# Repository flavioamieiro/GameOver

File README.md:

Hardware for Game Over project

[BaseBoard](BaseBoard/) contains the design files for the  main board, which
has an ESP32 and will be the base for the add-ons.

[BNO055Sensor](BNO055Sensor/) is the first add-on: basically a BNO055 sensor
from Adafruit used for motion detection.

[Keypad](Keypad/) is a keypad with six buttons and LEDs to be used as
an interface.

[BreakoutBoard](BreakoutBoard/) is a simple breakout board for easier
prototyping using the base board.

[AddonTemplate](AddonTemplate/) is a kicad template you can use as a base to
create new addon boards.

This source describes Open Hardware and is licensed under the CERN-OHL-S v2.
You may redistribute and modify this source and make products using it under
the terms of the [CERN-OHL-S v2](https://ohwr.org/cern_ohl_s_v2.txt).

Source location: https://github.com/flavioamieiro/GameOver

As per CERN-OHL-S v2 section 4, should You produce hardware based on this
source, You must where practicable maintain the Source Location visible on the
external case of the Gizmo or other products you make using this source.

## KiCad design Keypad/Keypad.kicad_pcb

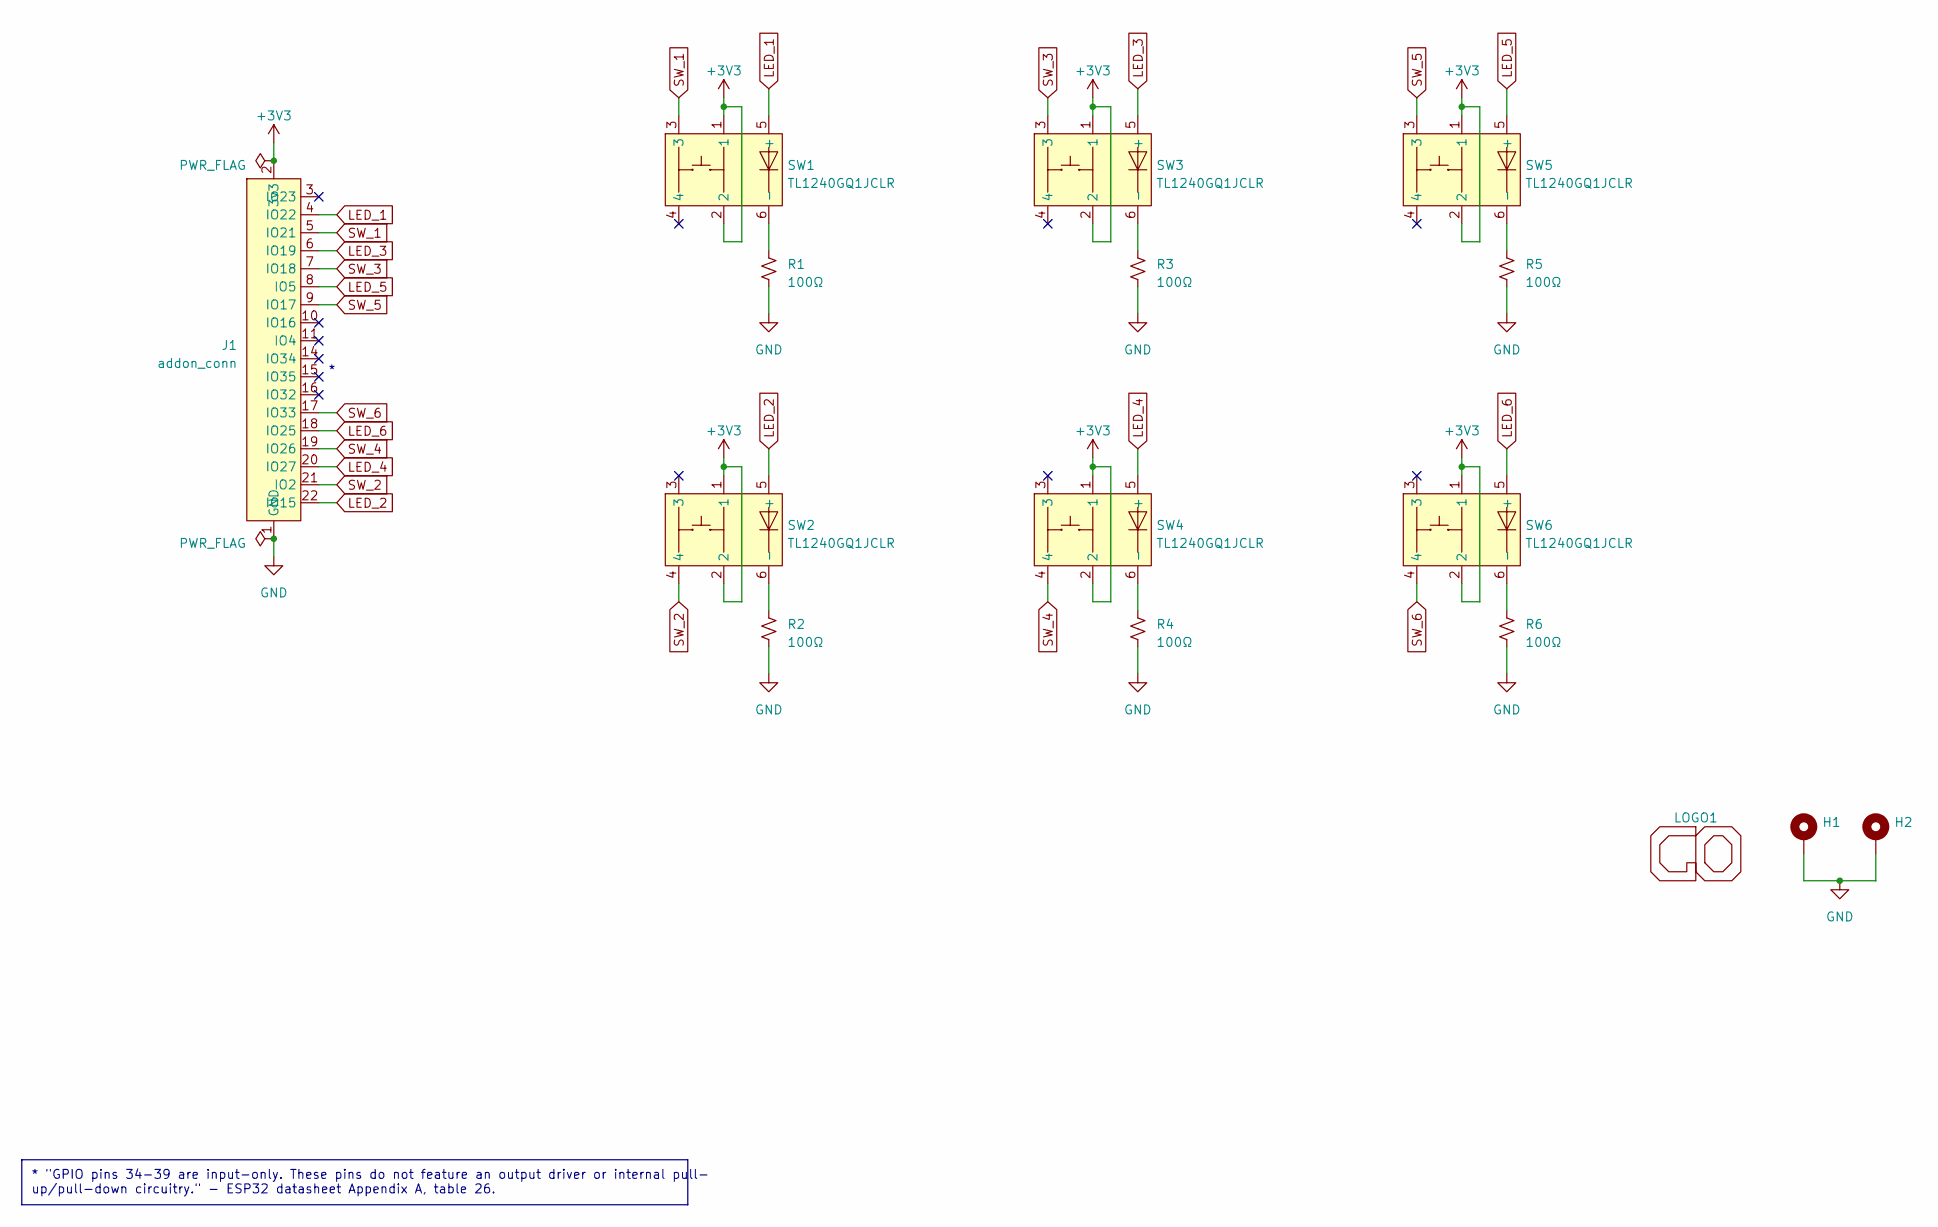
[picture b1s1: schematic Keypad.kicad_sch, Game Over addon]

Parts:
H1, H2: MountingHole_2.2mm_M2_Pad_Via
J1: addon_conn; Addon_conn_TXGA_FFC05036-24SBD113W5M_1x24_P0.50mm_Horizontal
LOGO1: GameOver_logo; logo_fcu
R1, R2, R3, R4, R5, R6: 100Ω; R_0805_2012Metric_Pad1.20x1.40mm_HandSolder
SW1, SW2, SW3, SW4, SW5, SW6: TL1240GQ1JCLR

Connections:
+3V3: J1.2 (3v3), J1.13 (3v3), J1.24 (3v3), SW1.1, SW1.2, SW2.1, SW2.2, SW3.1, SW3.2, SW4.1, SW4.2, SW5.1, SW5.2, SW6.1, SW6.2
GND: H1.1, H2.1, J1.1 (GND), J1.12 (GND), J1.23 (GND), R1.2, R2.2, R3.2, R4.2, R5.2, R6.2
LED_1: J1.4 (IO22), SW1.5 (+)
LED_2: J1.22 (IO15), SW2.5 (+)
LED_3: J1.6 (IO19), SW3.5 (+)
LED_4: J1.20 (IO27), SW4.5 (+)
LED_5: J1.8 (IO18), SW5.5 (+)
LED_6: J1.18 (IO25), SW6.5 (+)
unnamed: R1.1, SW1.6 (-)
unnamed: R2.1, SW2.6 (-)
unnamed: R3.1, SW3.6 (-)
unnamed: R4.1, SW4.6 (-)
unnamed: R5.1, SW5.6 (-)
unnamed: R6.1, SW6.6 (-)
SW_1: J1.5 (IO21), SW1.3
SW_2: J1.21 (IO2), SW2.4
SW_3: J1.7 (IO5), SW3.3
SW_4: J1.19 (IO26), SW4.4
SW_5: J1.9 (IO17), SW5.3
SW_6: J1.17 (IO33), SW6.4

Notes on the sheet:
* "GPIO pins 34-39 are input-only. These pins do not feature an output driver or internal pull- up/pull-down circuitry." - ESP32 datasheet Appendix A, table 26.

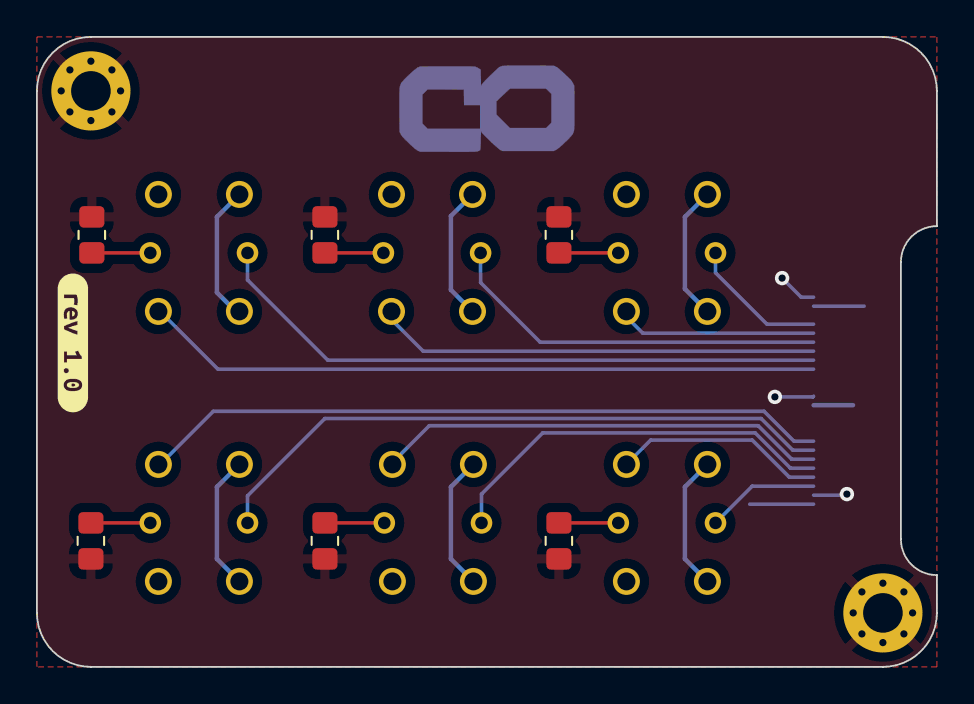
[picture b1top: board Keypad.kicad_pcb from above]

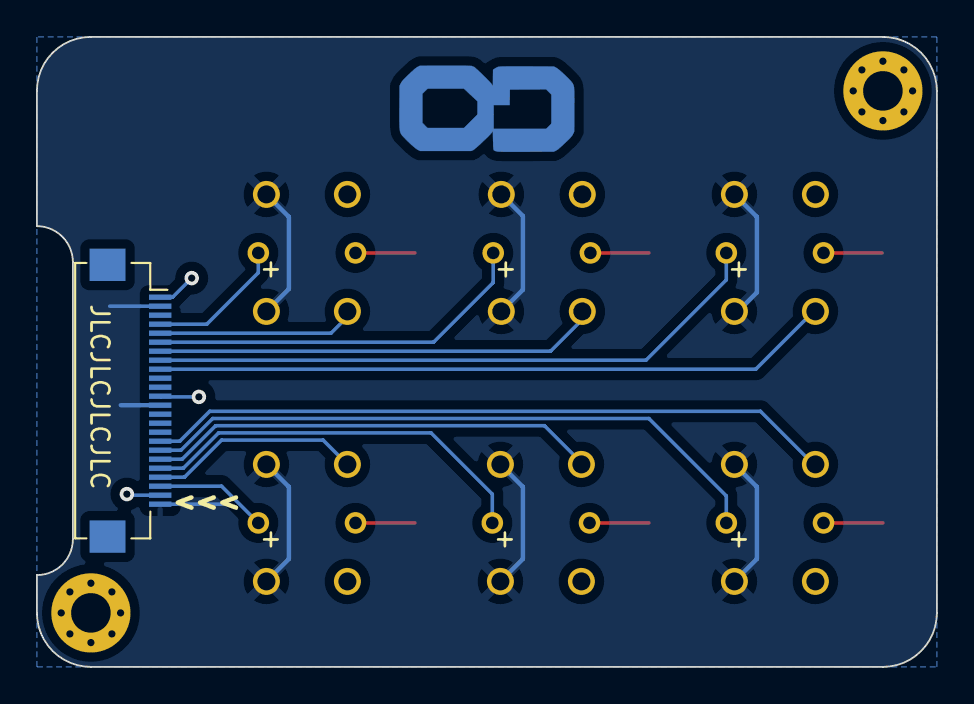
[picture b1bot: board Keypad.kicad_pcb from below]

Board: 2 copper layers, 50.0 x 35.0 mm, 17 parts (8 on the bottom side), 20 nets.

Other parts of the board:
kibuzzard-63029D1F: G***; kibuzzard-63029D1F

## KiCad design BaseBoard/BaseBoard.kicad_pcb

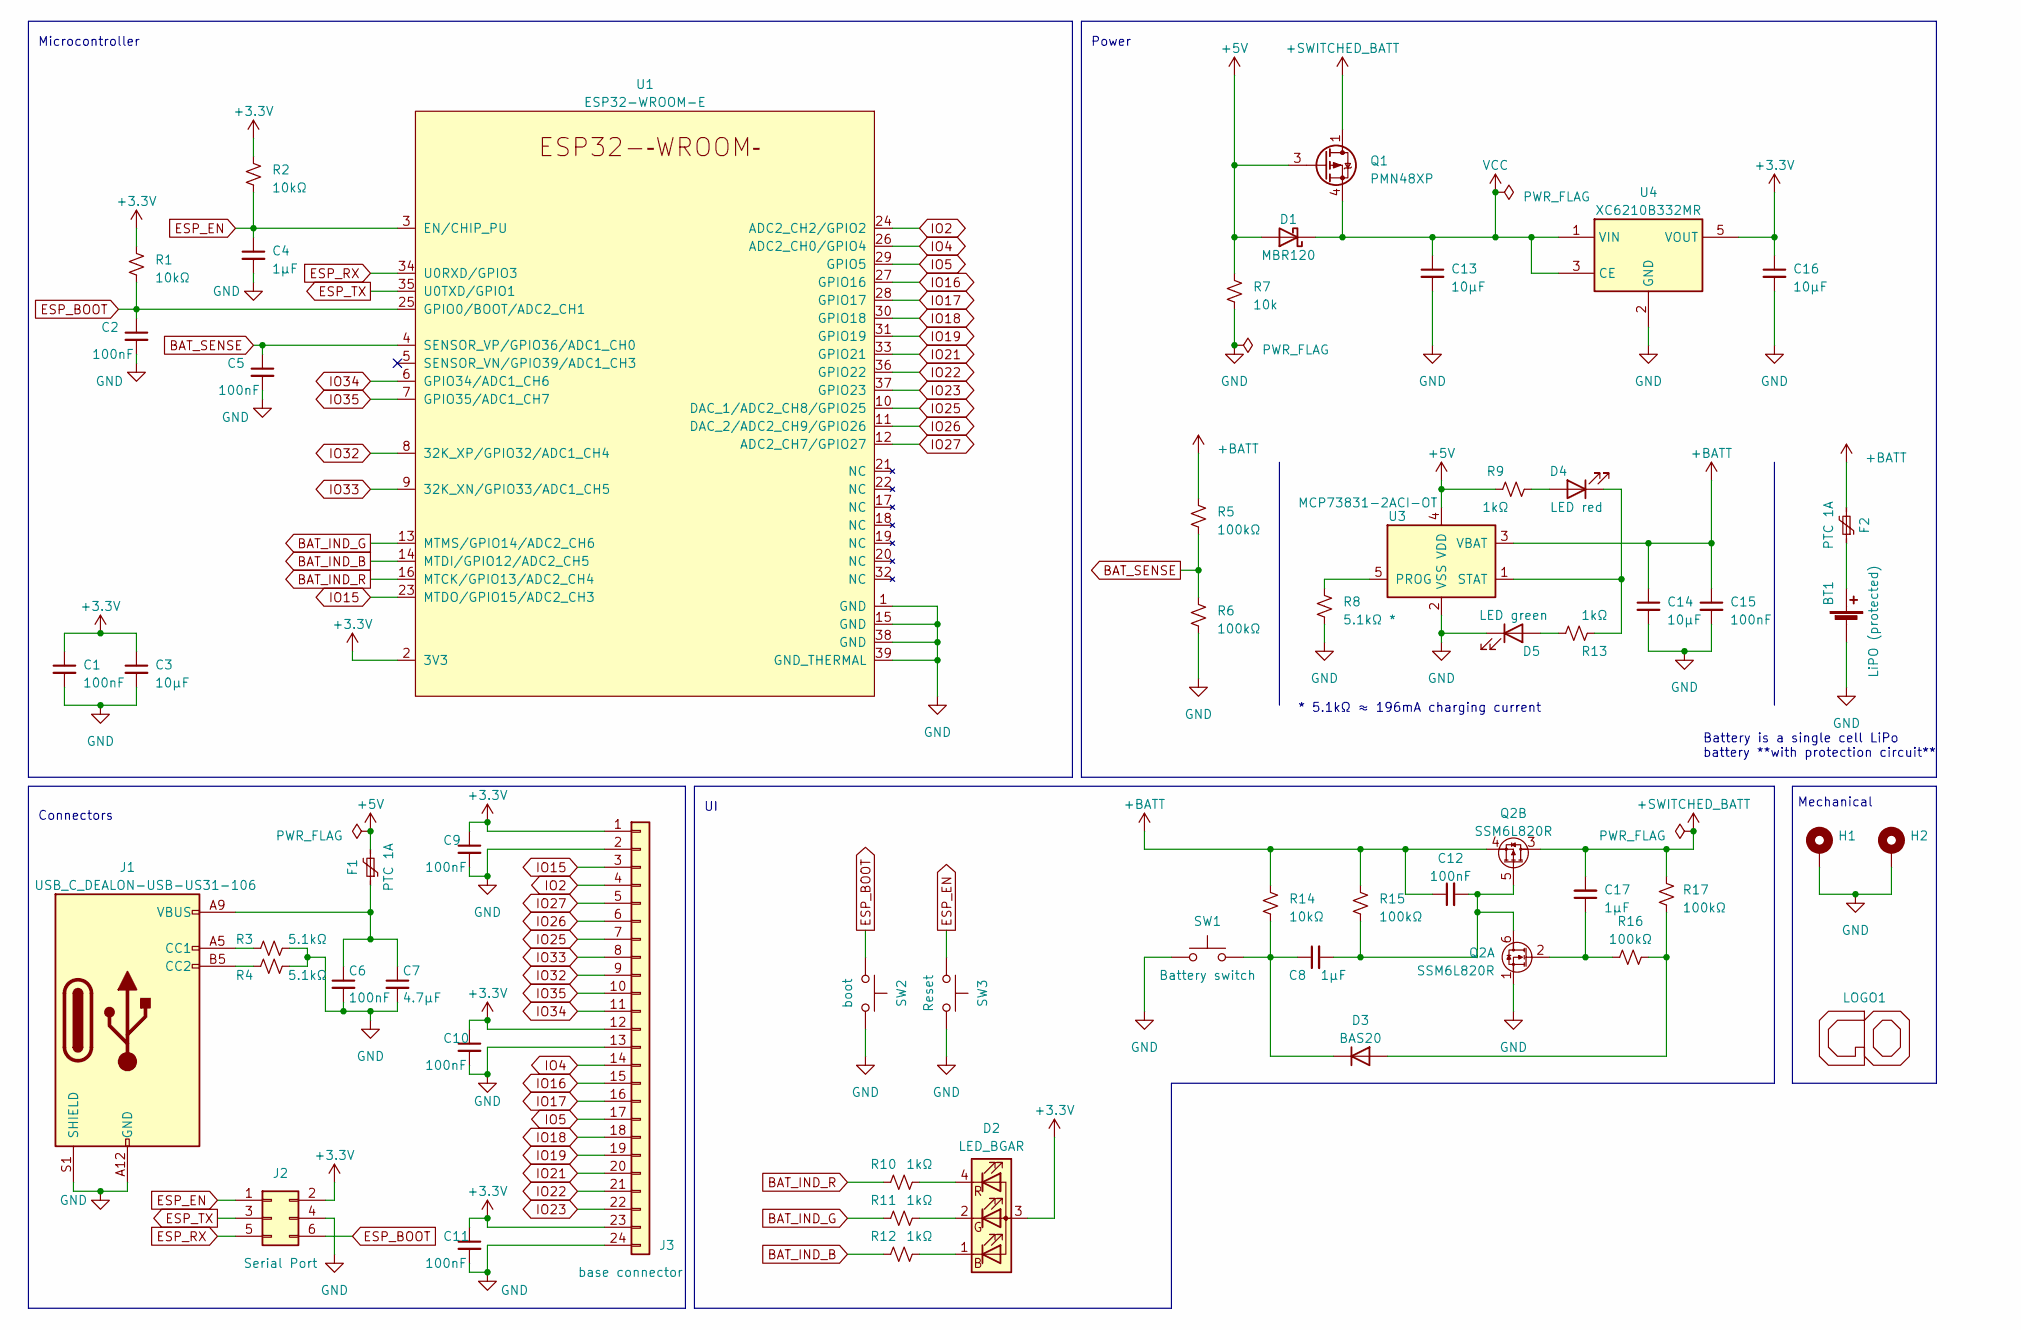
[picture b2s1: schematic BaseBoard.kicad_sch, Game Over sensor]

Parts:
BT1: LiPO (protected); JST_PH_S2B-PH-SM4-TB_1x02-1MP_P2.00mm_Horizontal
C1, C2, C5, C6, C9, C10, C11, C12, C15: 100nF; C_0805_2012Metric_Pad1.18x1.45mm_HandSolder
C3, C13, C14, C16: 10µF; C_0805_2012Metric_Pad1.18x1.45mm_HandSolder
C4, C8, C17: 1µF; C_0805_2012Metric_Pad1.18x1.45mm_HandSolder
C7: 4.7µF; C_0805_2012Metric_Pad1.18x1.45mm_HandSolder
D1: MBR120; D_SOD-123
D2: LED_BGAR; Hongzhi_Forest_HS-1204-RGB
D3: BAS20; SOT-23
D4: LED red; LED_0603_1608Metric
D5: LED green; LED_0603_1608Metric
F1, F2: PTC 1A; Belfuse_0ZCJ
H1, H2: MountingHole_2.2mm_M2_Pad_Via
J1: USB_C_DEALON-USB-US31-106; DEALON_USB-US31-106
J2: Serial Port; Tag-Connect_TC2030-IDC-FP_2x03_P1.27mm_Vertical
J3: base connector; Base_conn_TXGA_FFC05036-24SBD113W5M_1x24_P0.50mm_Horizontal
LOGO1: GameOver_logo; logo_fsilk
Q1: PMN48XP; TSOP-6_1.65x3.05mm_P0.95mm
Q2: SSM6L820R; TSOP6F
R1, R2, R14: 10kΩ; R_0805_2012Metric_Pad1.20x1.40mm_HandSolder
R3, R4: 5.1kΩ; R_0805_2012Metric_Pad1.20x1.40mm_HandSolder
R5, R6, R15, R16, R17: 100kΩ; R_0805_2012Metric_Pad1.20x1.40mm_HandSolder
R7: 10k; R_0805_2012Metric_Pad1.20x1.40mm_HandSolder
R8: 5.1kΩ *; R_0805_2012Metric_Pad1.20x1.40mm_HandSolder
R9, R10, R11, R12, R13: 1kΩ; R_0805_2012Metric_Pad1.20x1.40mm_HandSolder
SW1: Battery switch; SW_Tactile_SPST_SOFNG_TS-1814
SW2: boot; SW_Tactile_SPST_SOFNG_TS-1814
SW3: Reset; SW_Tactile_SPST_SOFNG_TS-1814
U1: ESP32-WROOM-E; ESP32-WROOM-32E
U3: MCP73831-2ACI-OT; SOT-23-5
U4: XC6210B332MR; SOT-23-5

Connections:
+3V3: C1.1, C3.1, C9.1, C10.1, C11.1, C16.1, D2.3 (A), J2.2, J3.1, J3.12, J3.23, R1.1, R2.1, U1.2 (3V3), U4.5 (VOUT)
+5V: D1.2 (A), F1.2, Q1.3 (G), R7.1, R9.2, U3.4 (VDD)
+BATT: C12.1, C14.1, C15.1, F2.2, Q2.4 (S), R5.1, R14.1, R15.1, U3.3 (VBAT)
+SWITCHED_BATT: C17.2, Q1.1 (D), Q1.2 (D), Q1.5 (D), Q1.6 (D), Q2.3 (D), R17.2
BAT_IND_B: R12.1, U1.14 (MTDI/GPIO12/ADC2_CH5)
BAT_IND_G: R11.1, U1.13 (MTMS/GPIO14/ADC2_CH6)
BAT_IND_R: R10.1, U1.16 (MTCK/GPIO13/ADC2_CH4)
BAT_SENSE: C5.1, R5.2, R6.1, U1.4 (SENSOR_VP/GPIO36/ADC1_CH0)
ESP_BOOT: C2.1, J2.6, R1.2, SW2.1, U1.25 (GPIO0/BOOT/ADC2_CH1)
ESP_EN: C4.1, J2.1, R2.2, SW3.1, U1.3 (EN/CHIP_PU)
ESP_RX: J2.5, U1.34 (U0RXD/GPIO3)
ESP_TX: J2.3, U1.35 (U0TXD/GPIO1)
GND: BT1.2 (-), C1.2, C2.2, C3.2, C4.2, C5.2, C6.2, C7.2, C9.2, C10.2, C11.2, C13.2, C14.2, C15.2, C16.2, D5.1 (K), H1.1, H2.1, J1.A12 (GND), J1.B12 (GND), J1.S1 (SHIELD), J2.4, J3.2, J3.13, J3.24, Q2.1 (S), R3.2, R4.2, R6.2, R7.2, R8.2, SW1.1, SW2.2, SW3.2, U1.1 (GND), U1.15 (GND), U1.38 (GND), U1.39 (GND_THERMAL), U3.2 (VSS), U4.2 (GND)
IO2: J3.4, U1.24 (ADC2_CH2/GPIO2)
IO4: J3.14, U1.26 (ADC2_CH0/GPIO4)
IO5: J3.17, U1.29 (GPIO5)
IO15: J3.3, U1.23 (MTDO/GPIO15/ADC2_CH3)
IO16: J3.15, U1.27 (GPIO16)
IO17: J3.16, U1.28 (GPIO17)
IO18: J3.18, U1.30 (GPIO18)
IO19: J3.19, U1.31 (GPIO19)
IO21: J3.20, U1.33 (GPIO21)
IO22: J3.21, U1.36 (GPIO22)
IO23: J3.22, U1.37 (GPIO23)
IO25: J3.7, U1.10 (DAC_1/ADC2_CH8/GPIO25)
IO26: J3.6, U1.11 (DAC_2/ADC2_CH9/GPIO26)
IO27: J3.5, U1.12 (ADC2_CH7/GPIO27)
IO32: J3.9, U1.8 (32K_XP/GPIO32/ADC1_CH4)
IO33: J3.8, U1.9 (32K_XN/GPIO33/ADC1_CH5)
IO34: J3.11, U1.6 (GPIO34/ADC1_CH6)
IO35: J3.10, U1.7 (GPIO35/ADC1_CH7)
unnamed: BT1.1 (+), F2.1
unnamed: D2.1 (BK), R12.2
unnamed: D2.2 (GK), R11.2
unnamed: D2.4 (RK), R10.2
unnamed: D3.1 (A), R16.2, R17.1
unnamed: C8.1, D3.3 (K), R14.2, SW1.2
unnamed: D4.2 (A), R9.1
unnamed: D4.1 (K), R13.2, U3.1 (STAT)
unnamed: D5.2 (A), R13.1
unnamed: J1.A5 (CC1), R3.1
unnamed: J1.B5 (CC2), R4.1
unnamed: C6.1, C7.1, F1.1, J1.A9 (VBUS), J1.B9 (VBUS)
unnamed: C8.2, C12.2, Q2.5 (G), Q2.6 (D), R15.2
unnamed: C17.1, Q2.2 (G), R16.1
unnamed: R8.1, U3.5 (PROG)
VCC: C13.1, D1.1 (K), Q1.4 (S), U4.1 (VIN), U4.3 (CE)

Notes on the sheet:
Microcontroller
Connectors
Battery is a single cell LiPo battery **with protection circuit**
Power
* 5.1kΩ ≈ 196mA charging current
Mechanical

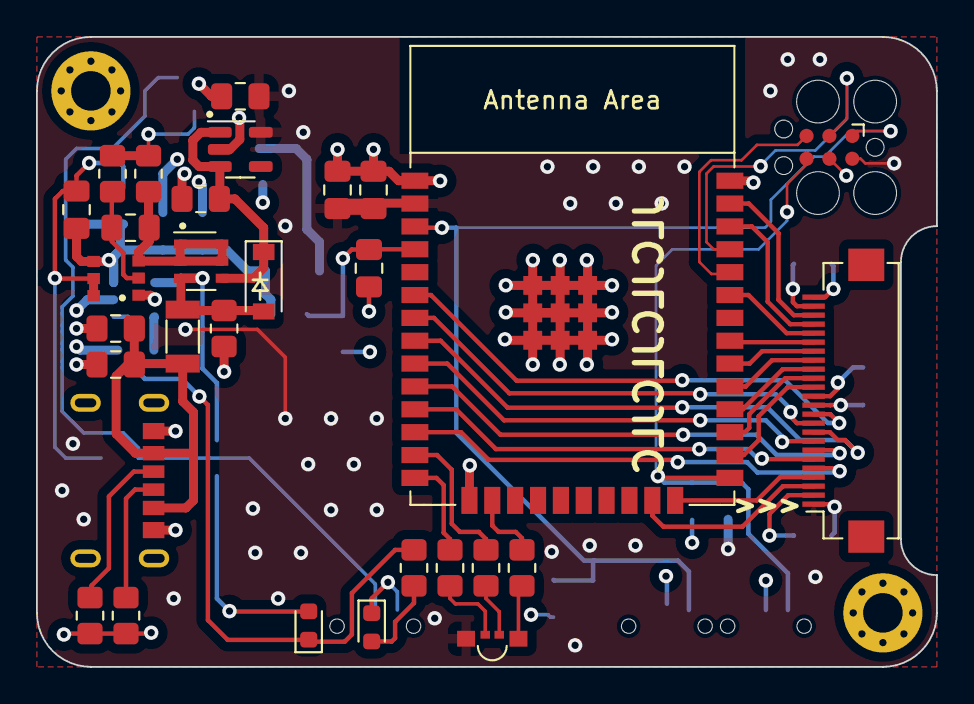
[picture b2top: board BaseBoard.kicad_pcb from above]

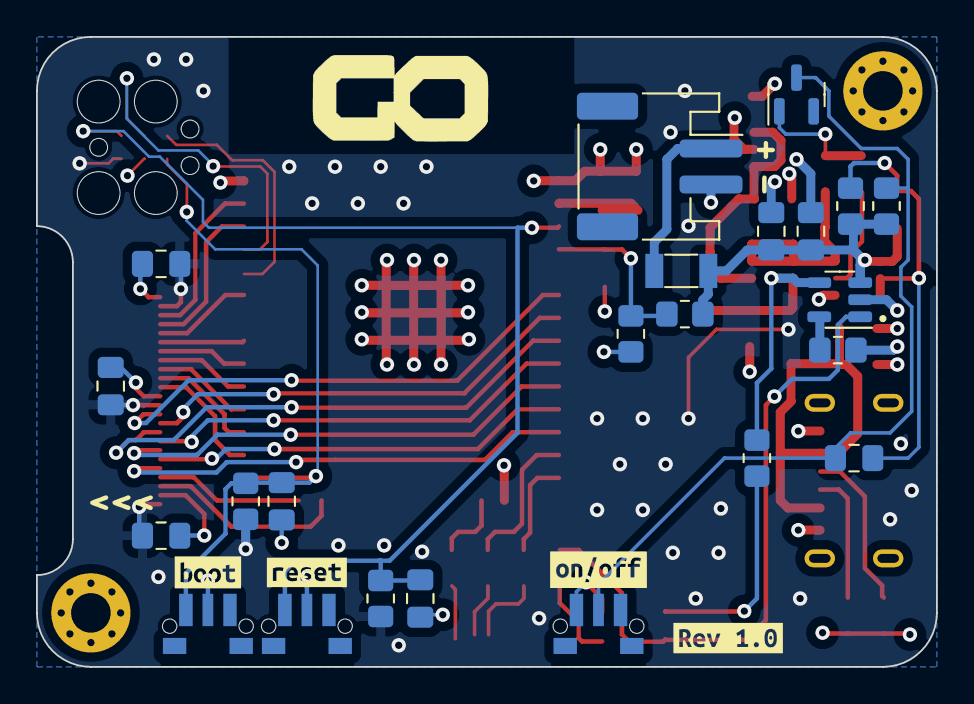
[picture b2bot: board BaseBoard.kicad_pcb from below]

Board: 4 copper layers, 50.0 x 35.0 mm, 60 parts (28 on the bottom side), 47 nets.

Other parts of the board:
kibuzzard-6253FE4C: G***; kibuzzard-6253FE4C
kibuzzard-6253FE42: G***; kibuzzard-6253FE42
kibuzzard-63029C06: G***; kibuzzard-63029C06
kibuzzard-63029CBF: G***; kibuzzard-63029CBF

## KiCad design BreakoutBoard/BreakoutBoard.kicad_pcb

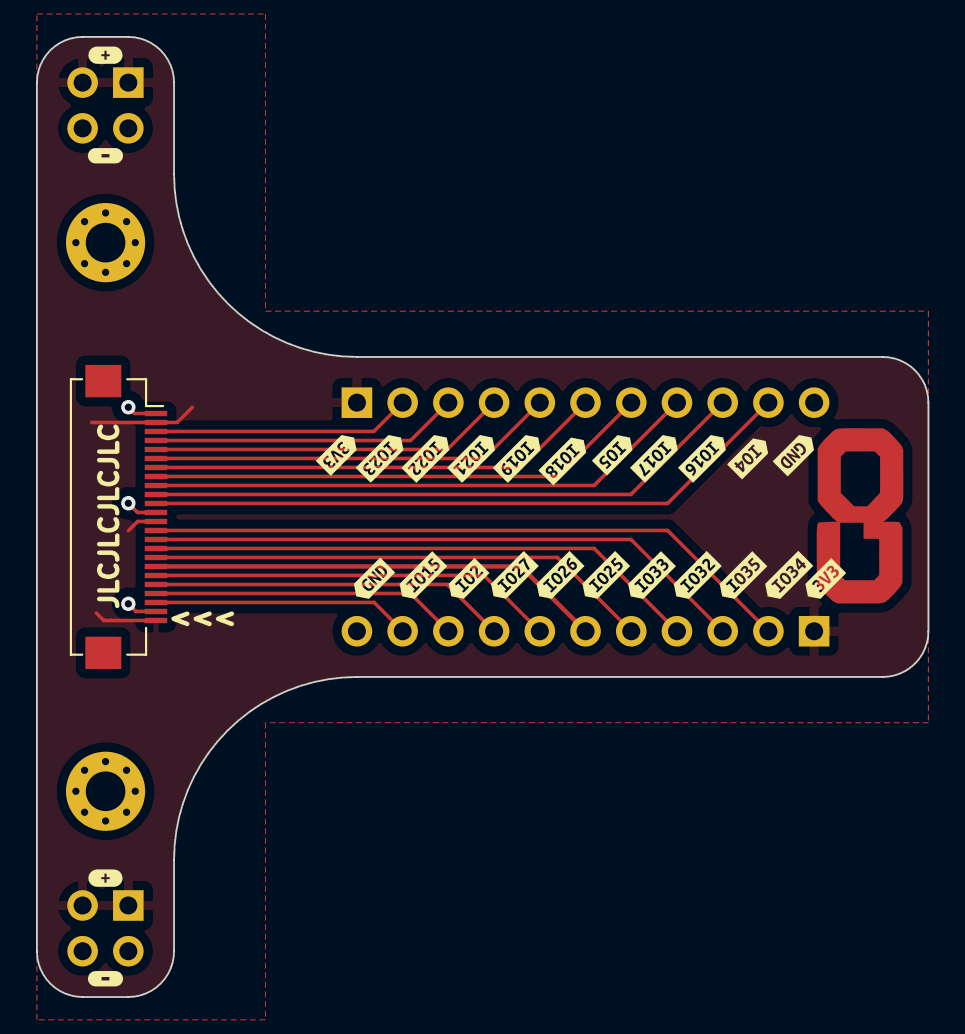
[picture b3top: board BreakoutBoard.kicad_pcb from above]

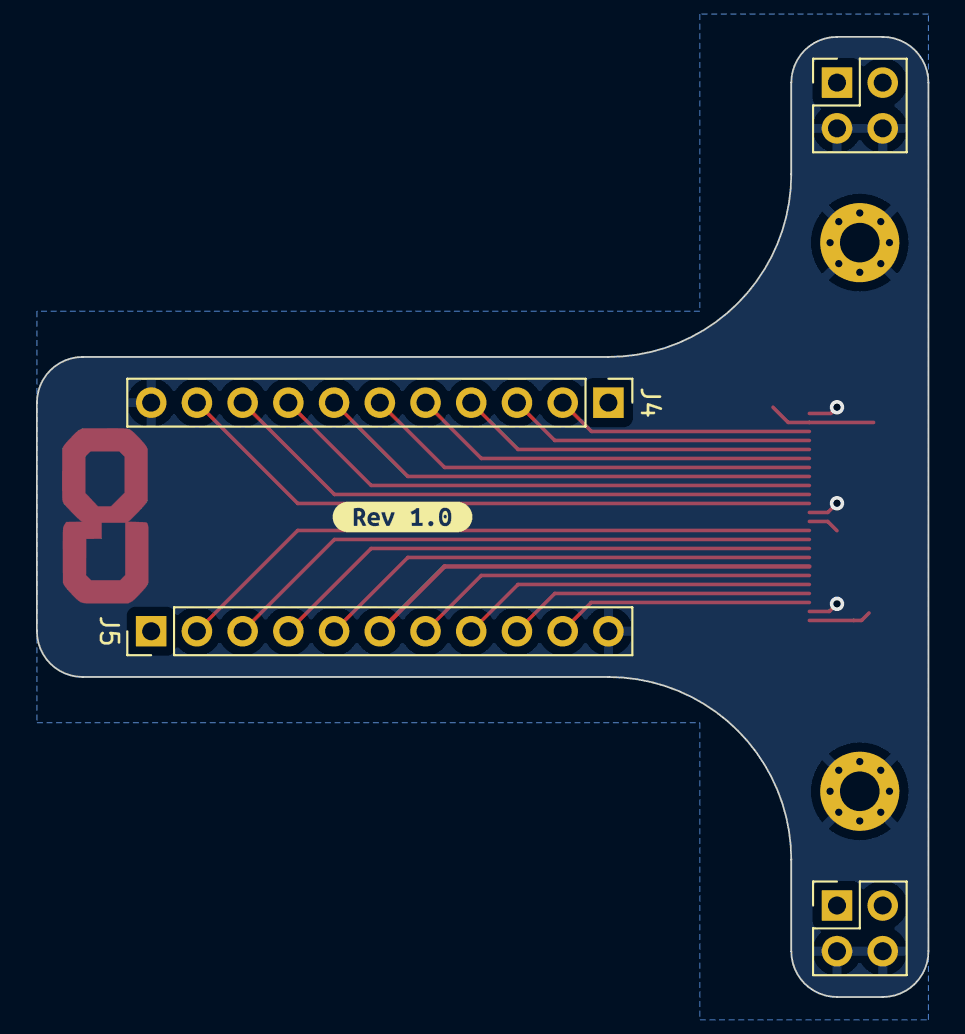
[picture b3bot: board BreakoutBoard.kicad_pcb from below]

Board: 2 copper layers, 49.5 x 53.3 mm, 35 parts (5 on the bottom side), 20 nets.

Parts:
H1, H2: MountingHole_2.2mm_M2_Pad_Via
J1: addon_conn; Addon_conn_TXGA_FFC05036-24SBD113W5M_1x24_P0.50mm_Horizontal
J2: Power_top; PinHeader_2x02_P2.54mm_Vertical
J3: Power_bottom; PinHeader_2x02_P2.54mm_Vertical
J4, J5: Conn_01x11; PinHeader_1x11_P2.54mm_Vertical
LOGO1: GameOver_logo; logo_fcu
kibuzzard-62829C43: G***; kibuzzard-62829C43
kibuzzard-62829C54: G***; kibuzzard-62829C54
kibuzzard-62829CE0: G***; kibuzzard-62829CE0
kibuzzard-62829D2F: G***; kibuzzard-62829D2F
kibuzzard-62829D15: G***; kibuzzard-62829D15
kibuzzard-62829D34: G***; kibuzzard-62829D34
kibuzzard-63029CFF: G***; kibuzzard-63029CFF
kibuzzard-625944D4: G***; kibuzzard-625944D4
kibuzzard-625944DF: G***; kibuzzard-625944DF
kibuzzard-625944E4: G***; kibuzzard-625944E4
kibuzzard-625944EE: G***; kibuzzard-625944EE
kibuzzard-625944F4: G***; kibuzzard-625944F4
kibuzzard-625944FA: G***; kibuzzard-625944FA
kibuzzard-625944FF: G***; kibuzzard-625944FF
kibuzzard-6259425C, kibuzzard-6259425C#2: G***; kibuzzard-6259425C
kibuzzard-6259452C: G***; kibuzzard-6259452C
kibuzzard-6259453A: G***; kibuzzard-6259453A
kibuzzard-6259453E: G***; kibuzzard-6259453E
kibuzzard-62594249, kibuzzard-62594249#2: G***; kibuzzard-62594249
kibuzzard-62594504: G***; kibuzzard-62594504
kibuzzard-62594508: G***; kibuzzard-62594508
kibuzzard-62594532: G***; kibuzzard-62594532
kibuzzard-62594542: G***; kibuzzard-62594542
kibuzzard-62594546: G***; kibuzzard-62594546
kibuzzard-62594559: G***; kibuzzard-62594559

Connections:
+3V3: J1.2 (3v3), J1.13 (3v3), J1.24 (3v3), J2.1, J2.2, J3.1, J3.2, J4.1, J5.1
GND: H1.1, H2.1, J1.1 (GND), J1.12 (GND), J1.23 (GND), J2.3, J2.4, J3.3, J3.4, J4.11, J5.11
unnamed: J1.21 (IO2), J5.9
unnamed: J1.11 (IO4), J4.10
unnamed: J1.8 (IO5), J4.7
unnamed: J1.22 (IO15), J5.10
unnamed: J1.10 (IO16), J4.9
unnamed: J1.9 (IO17), J4.8
unnamed: J1.7 (IO18), J4.6
unnamed: J1.6 (IO19), J4.5
unnamed: J1.5 (IO21), J4.4
unnamed: J1.4 (IO22), J4.3
unnamed: J1.3 (IO23), J4.2
unnamed: J1.18 (IO25), J5.6
unnamed: J1.19 (IO26), J5.7
unnamed: J1.20 (IO27), J5.8
unnamed: J1.16 (IO32), J5.4
unnamed: J1.17 (IO33), J5.5
unnamed: J1.14 (IO34), J5.2
unnamed: J1.15 (IO35), J5.3

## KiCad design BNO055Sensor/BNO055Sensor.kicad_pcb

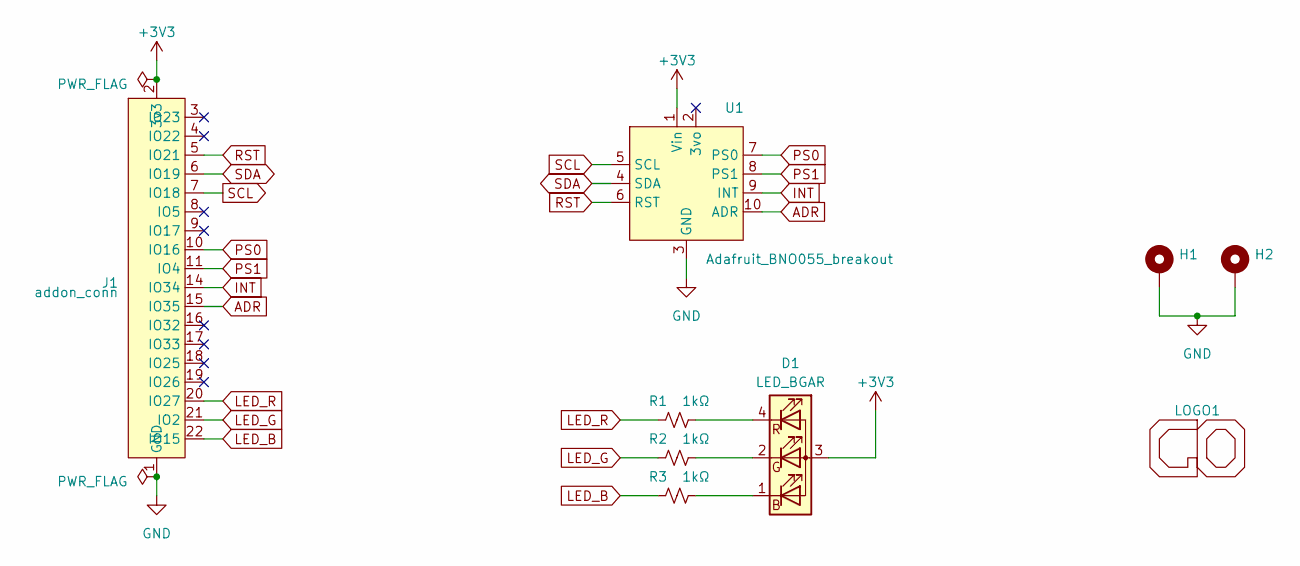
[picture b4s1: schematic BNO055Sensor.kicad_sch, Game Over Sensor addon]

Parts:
D1: LED_BGAR; Hongzhi_Forest_HS-1204-RGB
H1, H2: MountingHole_2.2mm_M2_Pad_Via
J1: addon_conn; Addon_conn_TXGA_FFC05036-24SBD113W5M_1x24_P0.50mm_Horizontal
LOGO1: GameOver_logo; logo_fcu
R1, R2, R3: 1kΩ; R_0805_2012Metric_Pad1.20x1.40mm_HandSolder
U1: Adafruit_BNO055_breakout

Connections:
+3V3: D1.3 (A), J1.2 (3v3), J1.13 (3v3), J1.24 (3v3), U1.1 (Vin)
ADR: J1.15 (IO35), U1.10 (ADR)
GND: H1.1, H2.1, J1.1 (GND), J1.12 (GND), J1.23 (GND), U1.3 (GND)
INT: J1.14 (IO34), U1.9 (INT)
LED_B: J1.22 (IO15), R3.1
LED_G: J1.21 (IO2), R2.1
LED_R: J1.20 (IO27), R1.1
unnamed: D1.1 (BK), R3.2
unnamed: D1.2 (GK), R2.2
unnamed: D1.4 (RK), R1.2
PS0: J1.10 (IO16), U1.7 (PS0)
PS1: J1.11 (IO4), U1.8 (PS1)
RST: J1.5 (IO21), U1.6 (RST)
SCL: J1.7 (IO18), U1.5 (SCL)
SDA: J1.6 (IO19), U1.4 (SDA)

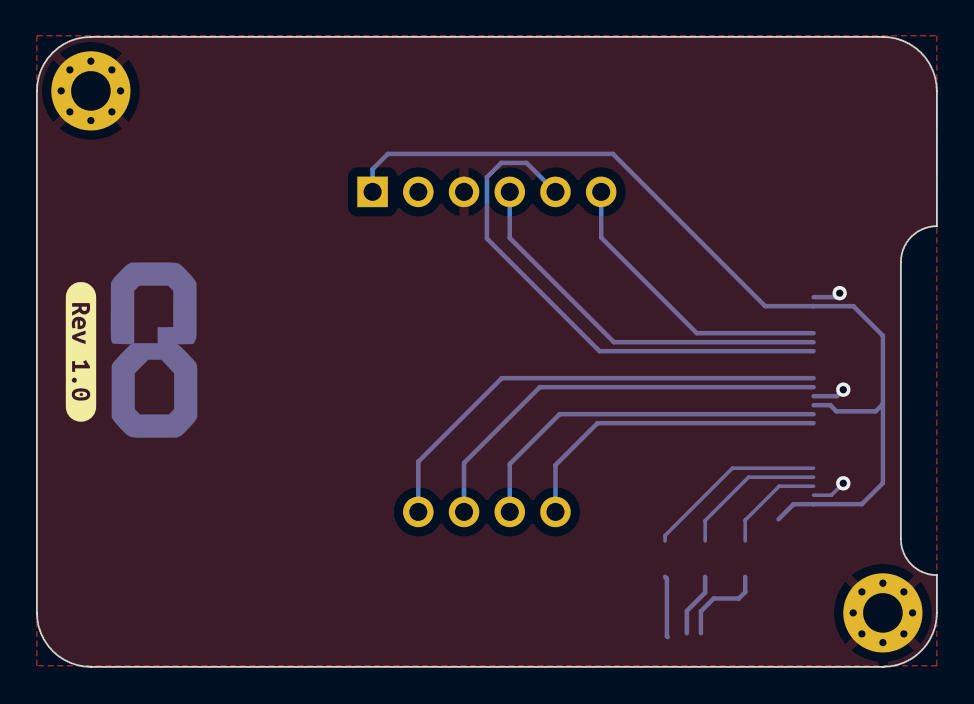
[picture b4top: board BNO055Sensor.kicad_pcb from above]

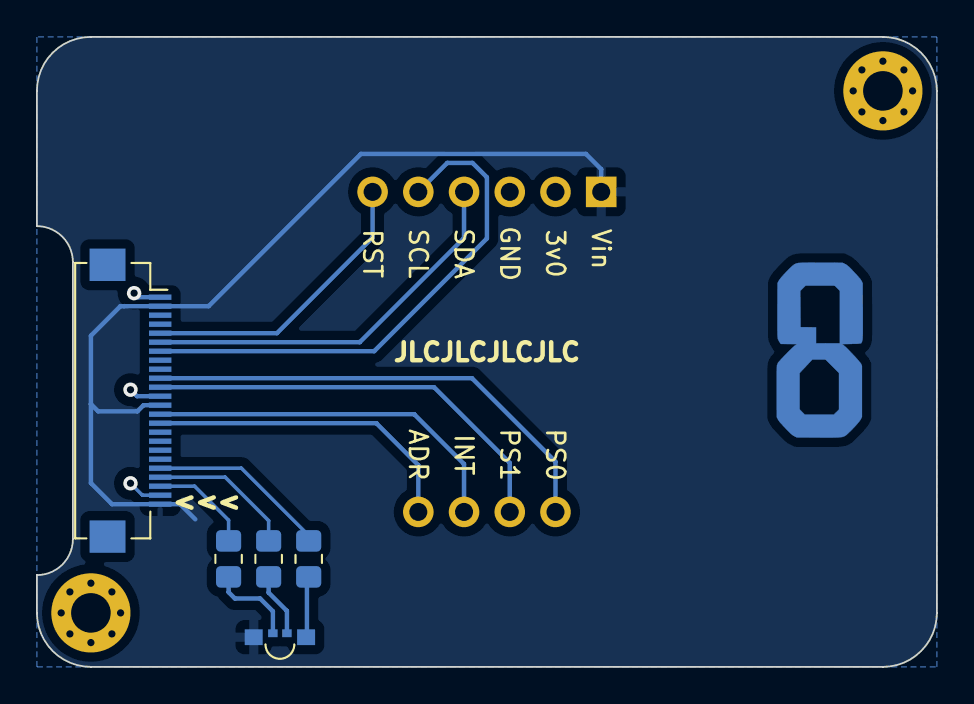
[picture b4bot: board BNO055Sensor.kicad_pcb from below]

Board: 2 copper layers, 50.0 x 35.0 mm, 10 parts (7 on the bottom side), 15 nets.

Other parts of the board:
kibuzzard-63029CE8: G***; kibuzzard-63029CE8

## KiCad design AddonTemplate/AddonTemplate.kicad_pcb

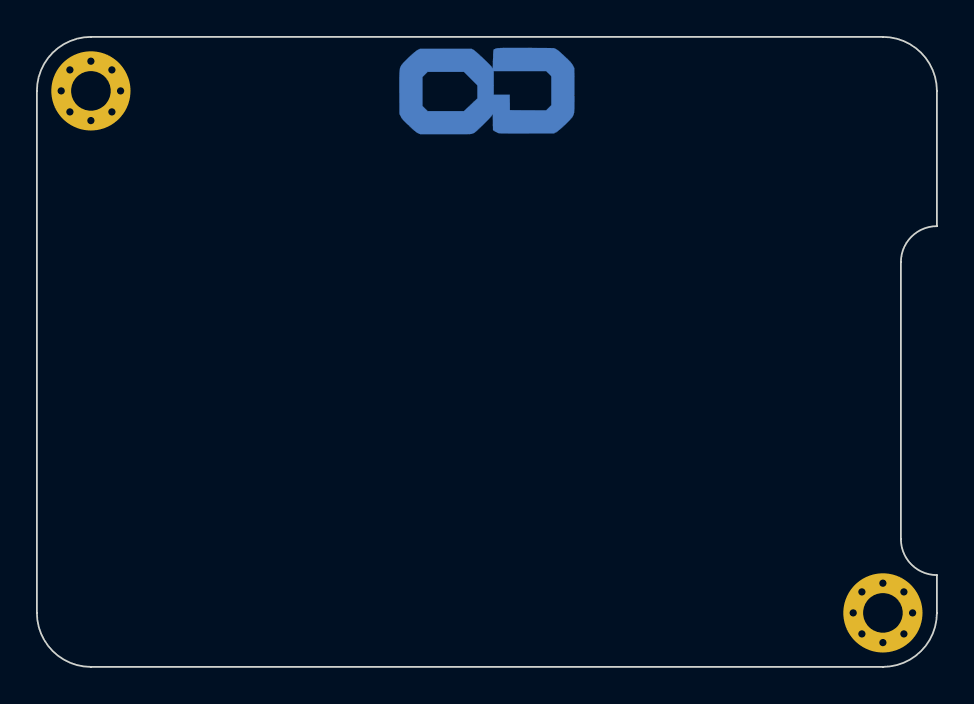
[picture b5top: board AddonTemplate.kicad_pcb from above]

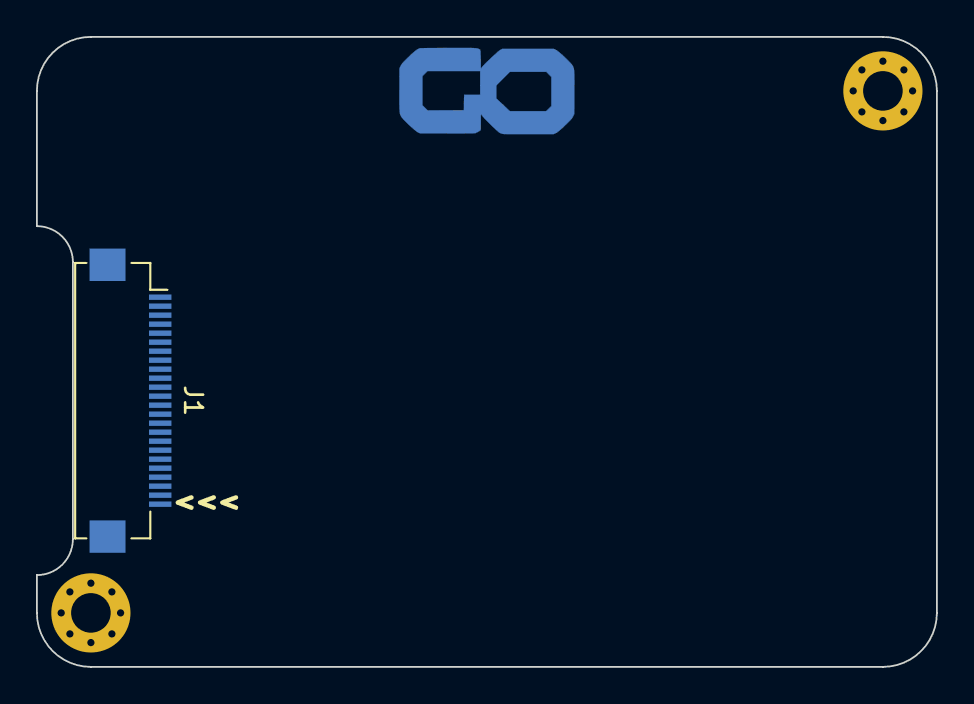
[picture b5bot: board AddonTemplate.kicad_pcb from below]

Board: 2 copper layers, 50.0 x 35.0 mm, 4 parts (2 on the bottom side), 2 nets, no tracks yet.

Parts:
H1, H2: MountingHole_2.2mm_M2_Pad_Via
J1: locked; Addon_conn_TXGA_FFC05036-24SBD113W5M_1x24_P0.50mm_Horizontal
LOGO1: GameOver_logo; logo_fcu

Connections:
+3V3: J1.2 (3v3), J1.13 (3v3), J1.24 (3v3)
GND: H1.1, H2.1, J1.1 (GND), J1.12 (GND), J1.23 (GND)
